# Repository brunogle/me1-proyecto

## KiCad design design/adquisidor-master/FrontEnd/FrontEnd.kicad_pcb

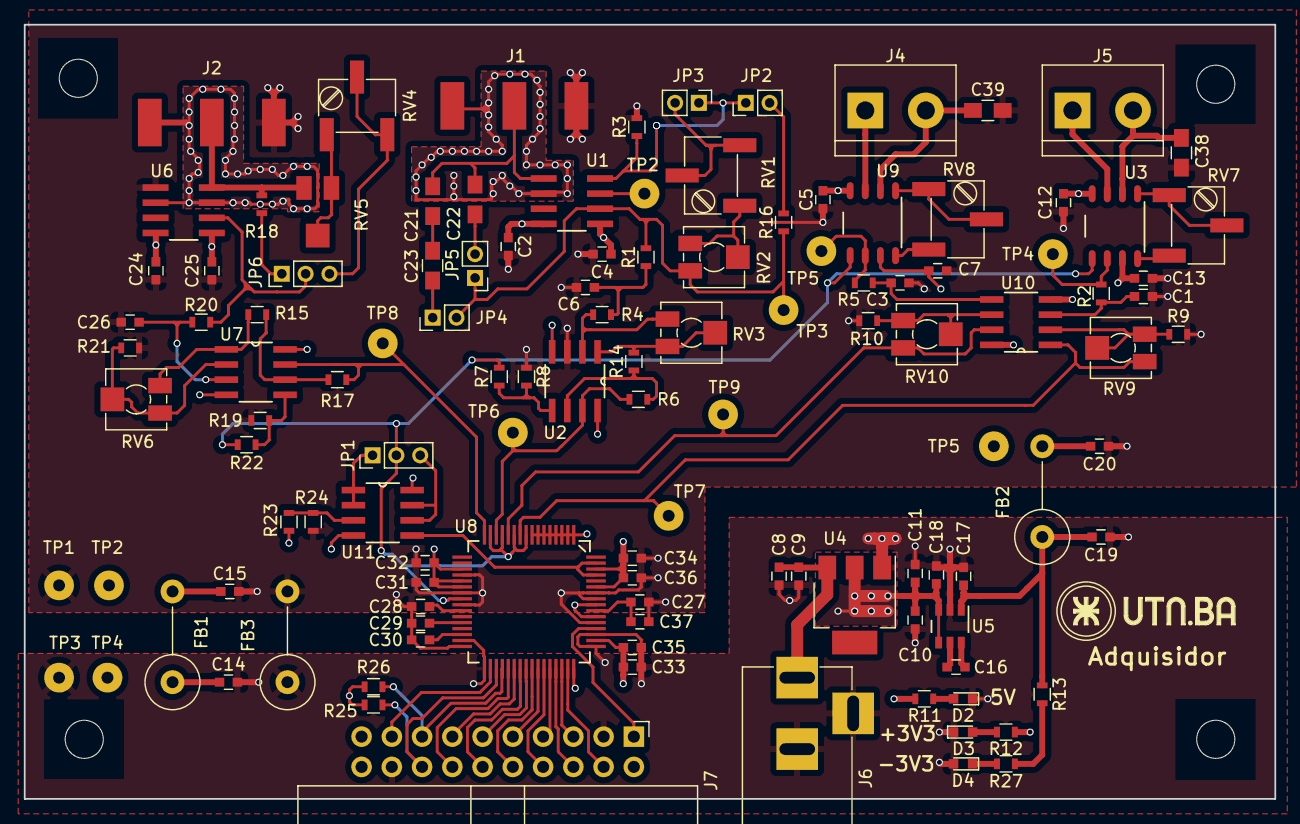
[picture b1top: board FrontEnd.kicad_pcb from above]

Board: 4 copper layers, 105.0 x 65.0 mm, 118 parts (0 on the bottom side), 82 nets.

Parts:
C1, C2, C3, C4, C5, C6, C7, C9, C10, C12, C13, C24, C25, C26, C32, C35, C36, C37: 100nF 10V; C_0603
C8, C11, C14, C15, C17, C19, C20: 10uF 10V; C_0603
C16, C18, C27, C31, C33, C34: 1uF 10V; C_0603
C21, C23, C39: 10pF 50V; C_0805_HandSoldering
C22, C38: 100pF 50V; C_0805_HandSoldering
C28, C30: 1µF 10V; C_0603
C29: 22µF 10V; C_0603
D2: Green; LED_0603
D3: Blue; LED_0603
D4: Red; LED_0603
FB1, FB2, FB3: Ferrite; L_Axial_L11.0mm_D4.5mm_P7.62mm_Vertical_Fastron_MECC
J1, J2: CONN_01X03; Triaxial_PAD
J4, J5: CONN_01X02; TerminalBlock_bornier-2_P5.08mm
J6: BARREL_JACK
J7: CONN_01X18; IDC-Header_2x10_Pitch2.54mm_Angled
JP1, JP6: JUMPER3; Pin_Header_Straight_1x03_Pitch2.00mm
JP2, JP3: JUMPER; Socket_Strip_Straight_1x02_Pitch2.00mm
JP4: J4; Pin_Header_Straight_1x02_Pitch2.00mm
JP5: J5; Socket_Strip_Straight_1x02_Pitch2.00mm
R1, R20, R27: 150R 1%; R_0603
R2, R5, R12, R21: 100R 1%; R_0603
R3, R6, R7, R8, R14, R15, R16, R17, R18, R19, R22, R23, R24, R25, R26: 10K 1%; R_0603
R4, R9, R10: 3K3 1%; R_0603
R11, R13: 470R 1%; R_0603
RV1, RV4, RV7, RV8: 10K; Potentiometer_Trimmer_Bourns_3269W
RV2, RV3, RV5, RV6, RV9, RV10: 200K; Potentiometer_Trimmer_Vishay_TS53YJ
TP1, TP2, TP2#2, TP3, TP3#2, TP4, TP4#2, TP5, TP5#2, TP6, TP7, TP8, TP9: TEST_1P; SolderWirePad_single_1mmDrill
U1, U6: ADA4530_1ARZ
U2, U7, U10, U11: TLC2272_D_8
U3, U9: INA828D; INA828IDR
U4: LD1117S33TR; SOT-223
U5: LM2776DBV; LM2776
U8: ADS1294_PAG_64; ADS1294

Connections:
+3V3: C10.1, C11.1, C14.1, C18.1, C33.1, C35.1, FB1.1, J7.2, R12.2, R25.1, R26.2, TP4#2.1, U4.2, U5.3, U5.4, U8.48, U8.50
+3V3A: C4.1, C7.2, C13.2, C15.1, C25.1, C31.1, C32.1, C34.1, C36.1, FB1.2, R23.1, TP2#2.1, U1.5, U2.8, U3.7, U6.5, U7.8, U8.1, U8.2, U8.3, U8.4, U8.5, U8.6, U8.7, U8.8, U8.19, U8.21, U8.22, U8.54, U8.56, U8.59, U8.62, U9.7, U10.8, U11.8
+5V: C8.1, C9.1, J6.1, R11.1, U4.3
-3V3: C17.1, C19.2, FB2.1, R13.1, U5.1
-3V3A: C2.1, C5.1, C12.1, C20.2, C24.1, FB2.2, TP5#2.1, U1.4, U2.4, U3.4, U6.4, U7.4, U9.4, U10.4, U11.4
/ADC y salida SPI/VoAVS: R6.2, TP6.1, U2.7, U8.14
/ADC y salida SPI/VoFF1: RV9.3, TP7.1, U8.10, U10.1
/ADC y salida SPI/VoFF2: RV10.1, TP9.1, U8.12, U10.7
/ADC y salida SPI/VoRMS: R17.2, TP8.1, U7.7, U8.16
/Campo Cercano_AVS/GRD1: J1.1, U1.2
/Campo Cercano_AVS/sIN1: C21.1, C22.1, J1.2, U1.1
/Campo Cercano_AVS/signal_OUT: JP4.2, JP5.1, R1.2, R16.1, RV2.1, TP3.1, U1.6
/Campo Cercano_RMS/GRD2: J2.1, U6.2, U6.7
/Campo Cercano_RMS/sIN2: J2.2, R18.2, RV5.1, U6.8
/Campo Cercano_RMS/signal_OUT: JP6.2, R20.2, U6.6
/CampoLejano1/sIN3: J5.1, U3.3
/CampoLejano1/sIN3n: C38.1, J5.2, U3.2
/CampoLejano1/sIN4: J4.1, U9.3
/CampoLejano1/sIN4n: C39.1, J4.2, U9.2
GND: C8.2, C9.2, C10.2, C11.2, C14.2, C17.2, C18.2, C19.1, C33.2, C35.2, D2.1, D3.1, D4.2, FB3.1, J6.2, J6.3, J7.3, J7.18, TP3#2.1, U4.1, U5.2, U8.31, U8.33, U8.49, U8.51
GNDA: C1.2, C2.2, C3.2, C4.2, C5.2, C6.2, C7.1, C12.2, C13.1, C15.2, C20.1, C24.2, C25.2, C26.2, C27.1, C28.2, C29.2, C30.2, C31.2, C32.2, C34.2, C36.2, C37.1, C38.2, C39.2, FB3.2, J1.3, J2.3, R3.2, R8.1, R9.1, R10.1, R19.1, R21.1, R24.1, TP1.1, U2.3, U6.1, U8.20, U8.23, U8.25, U8.32, U8.53, U8.57, U8.58
unnamed: C1.1, R2.1, U10.3
unnamed: C3.1, R5.1, U10.5
unnamed: C6.1, R1.1, R4.2
unnamed: C16.1, U5.5
unnamed: C16.2, U5.6
unnamed: C21.2, C23.1
unnamed: C22.2, JP5.2
unnamed: C23.2, JP4.1
unnamed: C26.1, R20.1, U7.3
unnamed: C27.2, C37.2, U8.55
unnamed: C28.1, U8.26
unnamed: C29.1, U8.28
unnamed: C30.1, U8.30
unnamed: D2.2, R11.2
unnamed: D3.2, R12.1
unnamed: D4.1, R27.2
unnamed: J7.1, U8.52
unnamed: J7.4, U8.47
unnamed: J7.5, U8.46
unnamed: J7.6, U8.45
unnamed: J7.7, U8.44
unnamed: J7.8, U8.43
unnamed: J7.9, U8.42
unnamed: J7.10, U8.41
unnamed: J7.11, U8.40
unnamed: J7.12, U8.39
unnamed: J7.13, U8.38
unnamed: J7.14, U8.37
unnamed: J7.15, R26.1, U8.36
unnamed: J7.16, R25.2, U8.35
unnamed: J7.17, U8.34
unnamed: JP1.1, U11.1, U11.2
unnamed: JP1.3, U11.6, U11.7
unnamed: JP2.1, JP3.1, R3.1, U1.8
unnamed: JP2.2, R16.2
unnamed: JP3.2, RV1.2, RV1.3
unnamed: JP6.1, R18.1
unnamed: JP6.3, RV4.2, RV4.3
unnamed: R2.2, TP4.1, U3.6
unnamed: R4.1, RV3.3, U2.2
unnamed: R5.2, TP5.1, U9.6
unnamed: R7.1, R8.2, U2.5
unnamed: R9.2, RV9.1, RV9.2, U10.2
unnamed: R10.2, RV10.2, RV10.3, U10.6
unnamed: R13.2, R27.1
unnamed: R6.1, R14.1, U2.6
unnamed: R14.2, RV3.1, RV3.2, U2.1
unnamed: R15.1, R17.1, U7.6
unnamed: R15.2, RV6.1, U7.1
unnamed: R19.2, R22.2, U7.5
unnamed: R21.2, RV6.2, RV6.3, U7.2
unnamed: R23.2, R24.2, U11.3
unnamed: RV1.1, RV2.2, RV2.3
unnamed: RV4.1, RV5.2, RV5.3
unnamed: RV7.1, RV7.2, U3.1
unnamed: RV7.3, U3.8
unnamed: RV8.1, RV8.2, U9.1
unnamed: RV8.3, U9.8
unnamed: TP2.1, U1.7
unnamed: U8.61, U8.63, U11.5
VCOM: JP1.2, R7.2, R22.1, U3.5, U8.9, U8.11, U8.13, U8.15, U8.24, U9.5

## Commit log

2023-10-05 Primer commit, funciones basicas para el ADC
2023-10-05 Agregue diseño del PCB
2024-02-12 Cambio a proyecto: ECG. Listo para entregar paper
2024-02-12 Primera Entrega
2024-02-16 D13 pulse during timer interrupt
2024-02-16 Mejoras en usabilidad del codigo
2024-02-18 Mejoras de codigo, comentarios
2024-03-02 Mayoria de correciones en el paper, analisis extra en calibracion
2024-03-03 Terminado v2 paper
2024-04-24 Comienzo de correcciones de v3
2024-05-22 Entregado paper v3

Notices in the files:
parts and their libraries:
Copyright 2016 Accelerated Designs. All rights reserved.
